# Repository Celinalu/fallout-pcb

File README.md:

### Totoro Keychain
Shake the totoro to watch the rain drops fall from the leaf!

# Slack ID
U09FBCFUA1Y

photos

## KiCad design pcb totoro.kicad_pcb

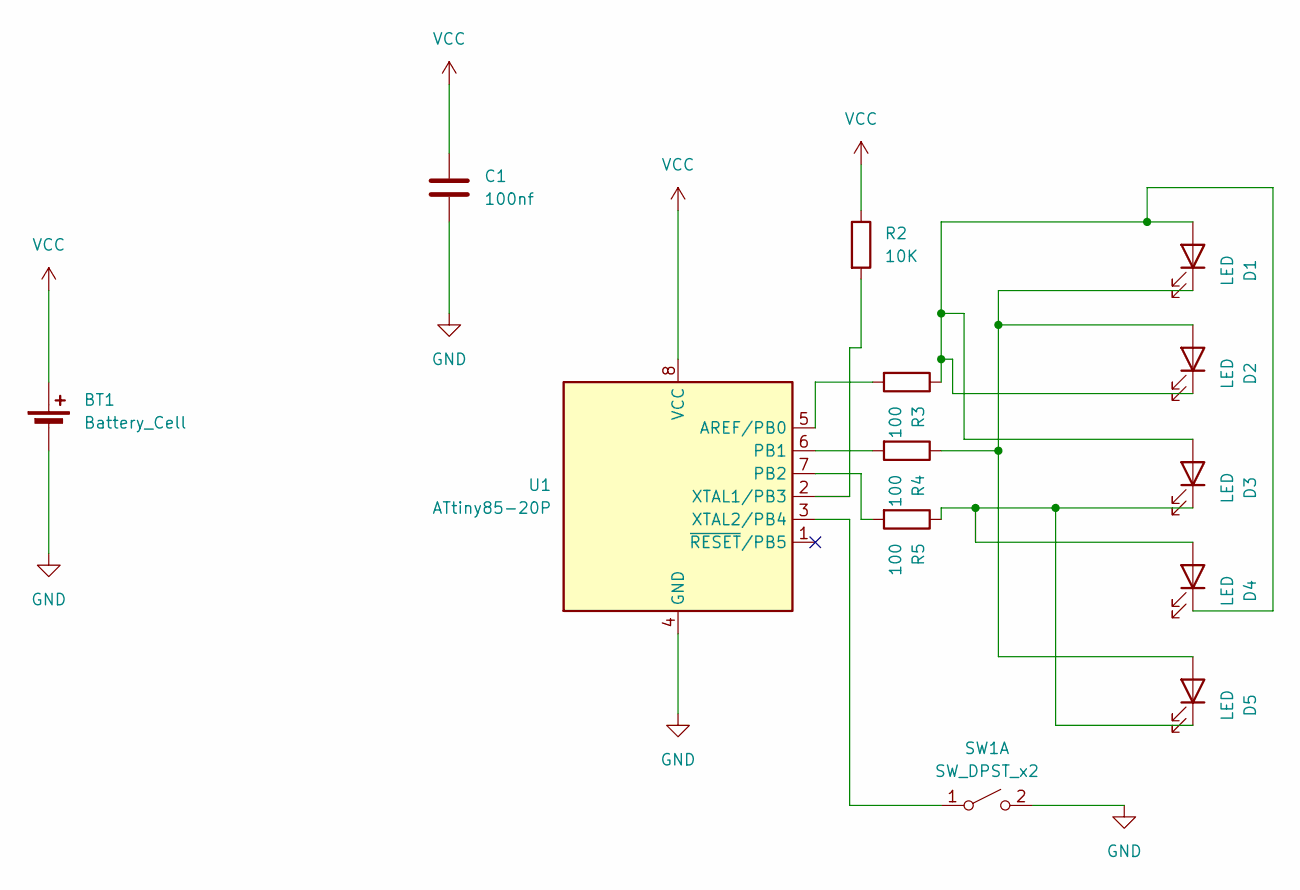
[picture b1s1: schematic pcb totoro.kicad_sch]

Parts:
BT1: Battery_Cell; BatteryHolder_Keystone_1058_1x2032
C1: 100nf; C_0805_2012Metric
D1, D2, D3, D4, D5: LED; LED_0805_2012Metric
R2: 10K; R_0805_2012Metric
R3, R4, R5: 100; R_0805_2012Metric
SW1: SW_DPST_x2; CP_Radial_D5.0mm_P2.50mm
U1: ATtiny85-20P; SOIC-8_3.9x4.9mm_P1.27mm

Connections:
GND: BT1.2 (-), C1.2, SW1.2 (B), U1.4 (GND)
unnamed: D1.2 (A), D2.1 (K), D3.2 (A), D4.1 (K), R3.1
unnamed: D1.1 (K), D2.2 (A), D5.2 (A), R4.1
unnamed: D3.1 (K), D4.2 (A), D5.1 (K), R5.1
unnamed: SW1.1 (A), U1.3 (XTAL2/PB4)
unnamed: R3.2, U1.5 (AREF/PB0)
unnamed: R4.2, U1.6 (PB1)
unnamed: R5.2, U1.7 (PB2)
unnamed: R2.2, U1.2 (XTAL1/PB3)
VCC: BT1.1 (+), C1.1, R2.1, U1.8 (VCC)

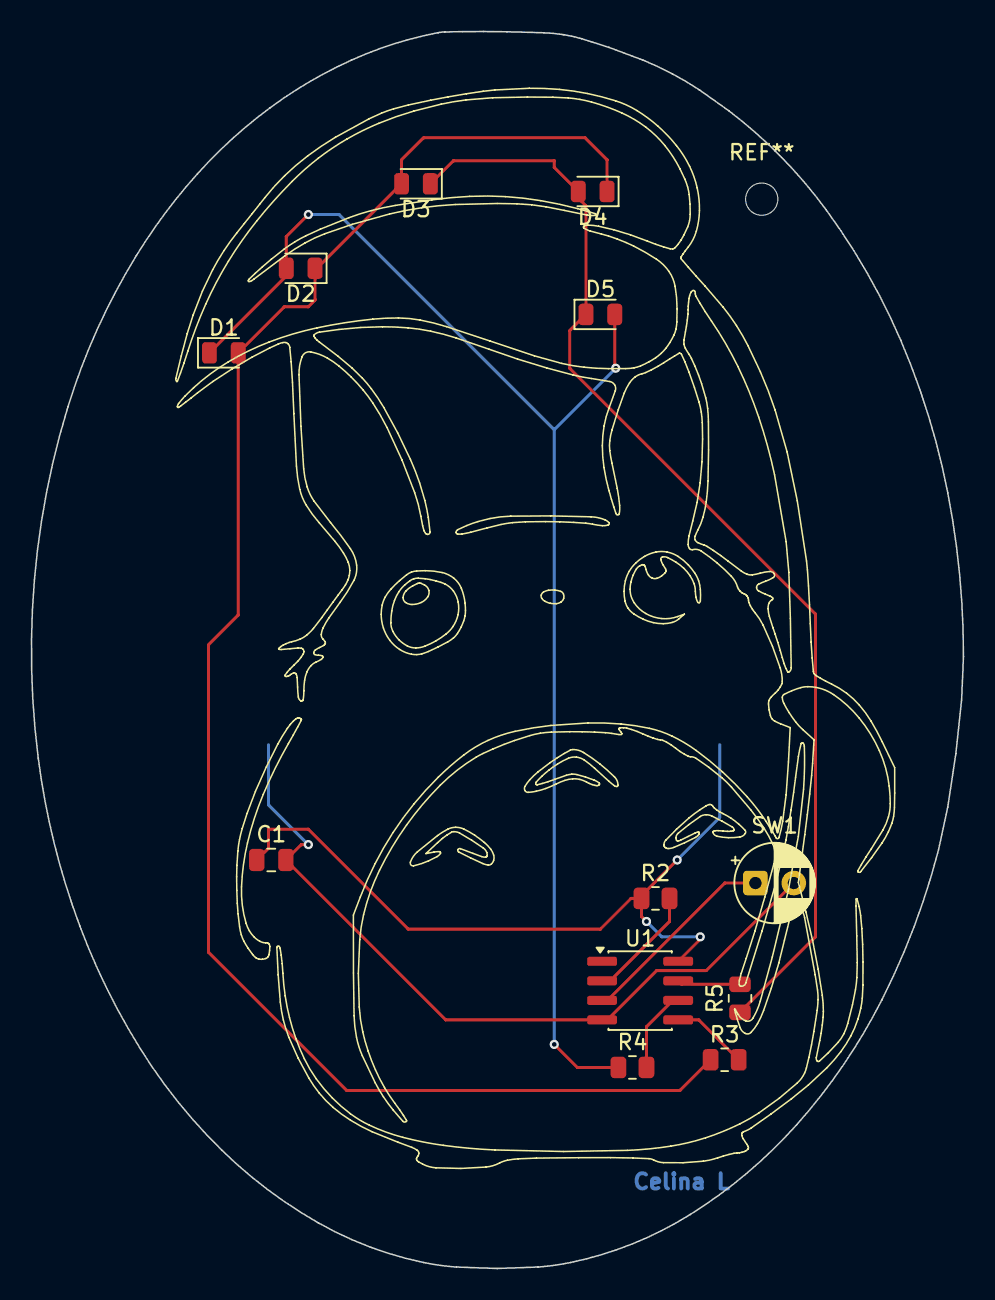
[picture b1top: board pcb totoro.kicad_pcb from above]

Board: 2 copper layers, 60.6 x 80.5 mm, 13 parts (1 on the bottom side), 10 nets.

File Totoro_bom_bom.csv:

Designator,Footprint,Quantity,Value,LCSC Part #
BT1,BatteryHolder_Keystone_1058_1x2032,1,Battery_Cell,
C1,0805,1,100nf,
"D1, D2, D3, D4, D5",0805,5,LED,
R2,0805,1,10K,
"R3, R4, R5",0805,3,100,
SW1,CP_Radial_D5.0mm_P2.50mm,1,SW_DPST_x2,
U1,SOIC-8_3.9x4.9mm_P1.27mm,1,ATtiny85-20P,
